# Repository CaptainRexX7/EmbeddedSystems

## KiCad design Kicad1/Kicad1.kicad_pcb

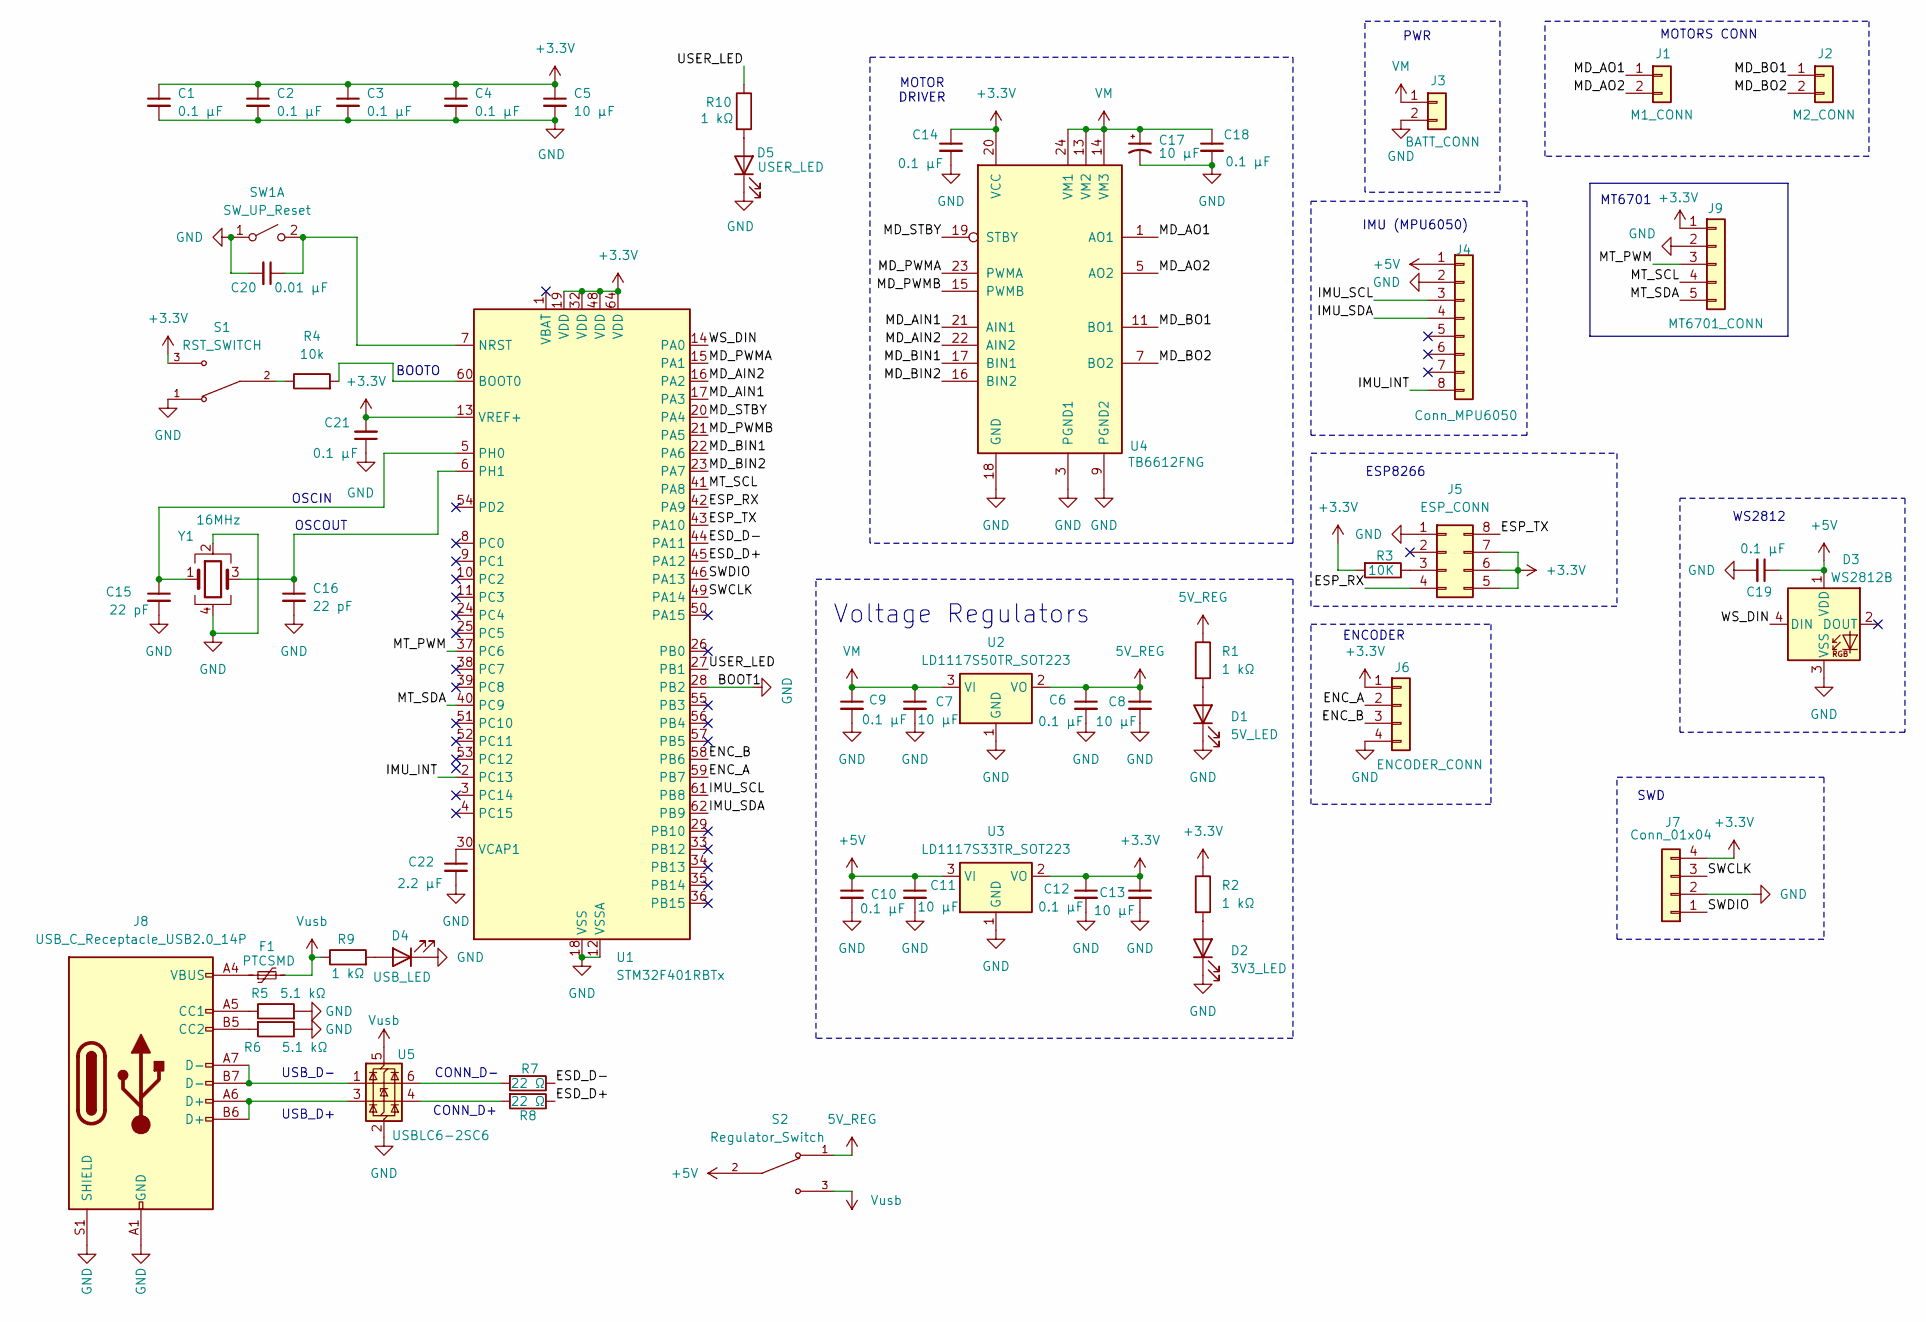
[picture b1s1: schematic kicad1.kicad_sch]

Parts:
C1, C2, C3, C4, C6, C9, C10, C12, C14, C18, C19, C21: 0.1 µF; C_0805_2012Metric_Pad1.18x1.45mm_HandSolder; Mfr#: KYOCERAAVX
C5: 10 µF; C_0805_2012Metric_Pad1.18x1.45mm_HandSolder
C7, C8, C11, C13: 10 µF; C_0805_2012Metric_Pad1.18x1.45mm_HandSolder; Mfr#: KYOCERAAVX
C15, C16: 22 pF; C_0805_2012Metric_Pad1.18x1.45mm_HandSolder
C17: 10 µF; CP_EIA-6032-28_Kemet-C_HandSolder
C20: 0.01 µF; C_0805_2012Metric_Pad1.18x1.45mm_HandSolder; Mfr#: KYOCERAAVX
C22: 2.2 µF; C_0805_2012Metric_Pad1.18x1.45mm_HandSolder
D1: 5V_LED; LED_0805_2012Metric_Pad1.15x1.40mm_HandSolder
D2: 3V3_LED; LED_0805_2012Metric_Pad1.15x1.40mm_HandSolder
D3: WS2812B; LED_WS2812B_PLCC4_5.0x5.0mm_P3.2mm
D4: USB_LED; LED_0805_2012Metric_Pad1.15x1.40mm_HandSolder
D5: USER_LED; LED_0805_2012Metric_Pad1.15x1.40mm_HandSolder
F1: PTCSMD; Fuse_1812_4532Metric
J1: M1_CONN; JST_XH_B2B-XH-A_1x02_P2.50mm_Vertical
J2: M2_CONN; JST_XH_B2B-XH-A_1x02_P2.50mm_Vertical
J3: BATT_CONN; JST_XH_B2B-XH-A_1x02_P2.50mm_Vertical
J4: Conn_MPU6050; PinSocket_1x08_P2.54mm_Vertical
J5: ESP_CONN; PinSocket_2x04_P2.54mm_Vertical
J6: ENCODER_CONN; JST_XH_B4B-XH-A_1x04_P2.50mm_Vertical
J7: Conn_01x04; PinHeader_1x04_P2.54mm_Vertical
J8: USB_C_Receptacle_USB2.0_14P; USB_C_Receptacle_HCTL_HC-TYPE-C-16P-01A
J9: MT6701_CONN; JST_XH_B5B-XH-A_1x05_P2.50mm_Vertical
R1, R2, R9, R10: 1 kΩ; R_0805_2012Metric_Pad1.20x1.40mm_HandSolder
R3: 10K; R_0805_2012Metric_Pad1.20x1.40mm_HandSolder
R4: 10k; R_0805_2012Metric_Pad1.20x1.40mm_HandSolder
R5, R6: 5.1 kΩ; R_0603_1608Metric_Pad0.98x0.95mm_HandSolder
R7, R8: 22 Ω; R_0805_2012Metric_Pad1.20x1.40mm_HandSolder
S1: RST_SWITCH; SW_SLW-66527511-SMT-TR; PARTREV 1.01
S2: Regulator_Switch; SW_SLW-66527511-SMT-TR; PARTREV 1.01
SW1: SW_UP_Reset; SW_uP_Reset
U1: STM32F401RBTx; LQFP-64_10x10mm_P0.5mm; mfr# STM32F401RET6
U2: LD1117S50TR_SOT223; SOT-223-3_TabPin2
U3: LD1117S33TR_SOT223; SOT-223-3_TabPin2
U4: TB6612FNG; SSOP-24_5.3x8.2mm_P0.65mm
U5: USBLC6-2SC6; SOT-23-6
Y1: 16MHz; Crystal_SMD_Abracon_ABM8G-4Pin_3.2x2.5mm

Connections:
5V_REG: C6.1, C8.1, R1.1, S2.1, U2.2 (VO)
+3.3V: C1.1, C2.1, C3.1, C4.1, C5.1, C12.1, C13.1, C14.1, C21.2, J5.5, J5.6, J5.7, J6.1, J7.4, J9.1, R2.1, R3.2, S1.3, U1.13 (VREF+), U1.19 (VDD), U1.32 (VDD), U1.48 (VDD), U1.64 (VDD), U3.2 (VO), U4.20 (VCC)
+5V: C10.1, C11.1, C19.1, D3.1 (VDD), J4.1, S2.2, U3.3 (VI)
/ENC_A: J6.2, U1.59 (PB7)
/ENC_B: J6.3, U1.58 (PB6)
/ESD_D+: R8.1, U1.45 (PA12)
/ESD_D-: R7.1, U1.44 (PA11)
/ESP_RX: J5.4, U1.42 (PA9)
/ESP_TX: J5.8, U1.43 (PA10)
/IMU_INT: J4.8, U1.2 (PC13)
/IMU_SCL: J4.3, U1.61 (PB8)
/IMU_SDA: J4.4, U1.62 (PB9)
/MD_AIN1: U1.17 (PA3), U4.21 (AIN1)
/MD_AIN2: U1.16 (PA2), U4.22 (AIN2)
/MD_AO1: J1.1, U4.1 (AO1), U4.2 (AO1)
/MD_AO2: J1.2, U4.5 (AO2), U4.6 (AO2)
/MD_BIN1: U1.22 (PA6), U4.17 (BIN1)
/MD_BIN2: U1.23 (PA7), U4.16 (BIN2)
/MD_BO1: J2.1, U4.11 (BO1), U4.12 (BO1)
/MD_BO2: J2.2, U4.7 (BO2), U4.8 (BO2)
/MD_PWMA: U1.15 (PA1), U4.23 (PWMA)
/MD_PWMB: U1.21 (PA5), U4.15 (PWMB)
/MD_STBY: U1.20 (PA4), U4.19 (STBY)
/MT_PWM: J9.3, U1.37 (PC6)
/MT_SCL: J9.4, U1.41 (PA8)
/MT_SDA: J9.5, U1.40 (PC9)
/SWCLK: J7.3, U1.49 (PA14)
/SWDIO: J7.1, U1.46 (PA13)
/USER_LED: R10.1, U1.27 (PB1)
/WS_DIN: D3.4 (DIN), U1.14 (PA0)
GND: C1.2, C2.2, C3.2, C4.2, C5.2, C6.2, C7.2, C8.2, C9.2, C10.2, C11.2, C12.2, C13.2, C14.2, C15.2, C16.2, C17.2, C18.2, C19.2, C20.2, C21.1, C22.2, D1.1 (K), D2.1 (K), D3.3 (VSS), D4.1 (K), D5.1 (K), J3.2, J4.2, J5.1, J6.4, J7.2, J8.A1 (GND), J8.A12 (GND), J8.B1 (GND), J8.B12 (GND), J8.S1 (SHIELD), J9.2, R5.2, R6.1, S1.1, SW1.1 (A), U1.12 (VSSA), U1.18 (VSS), U1.28 (PB2), U1.31 (VSS), U1.47 (VSS), U1.63 (VSS), U2.1 (GND), U3.1 (GND), U4.3 (PGND1), U4.4 (PGND1), U4.9 (PGND2), U4.10 (PGND2), U4.18 (GND), U5.2 (GND), Y1.2, Y1.4
unnamed: D1.2 (A), R1.2
unnamed: D2.2 (A), R2.2
unnamed: D4.2 (A), R9.2
unnamed: D5.2 (A), R10.2
unnamed: F1.1, J8.A4 (VBUS), J8.A9 (VBUS), J8.B4 (VBUS), J8.B9 (VBUS)
unnamed: J5.3, R3.1
unnamed: J8.A5 (CC1), R5.1
unnamed: J8.B5 (CC2), R6.2
unnamed: J8.A6 (D+), J8.B6 (D+), U5.3 (I/O2)
unnamed: J8.A7 (D-), J8.B7 (D-), U5.1 (I/O1)
unnamed: R4.1, S1.2
unnamed: R7.2, U5.6 (I/O1)
unnamed: R8.2, U5.4 (I/O2)
unnamed: C20.1, SW1.2 (B), U1.7 (NRST)
unnamed: R4.2, U1.60 (BOOT0)
unnamed: C15.1, U1.5 (PH0), Y1.1
unnamed: C16.1, U1.6 (PH1), Y1.3
unnamed: C22.1, U1.30 (VCAP1)
VM: C7.1, C9.1, C17.1, C18.1, J3.1, U2.3 (VI), U4.13 (VM2), U4.14 (VM3), U4.24 (VM1)
Vusb: F1.2, R9.1, S2.3, U5.5 (VBUS)

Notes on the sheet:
OSCIN
Voltage Regulators
PWR
MT6701
SWD
CONN_D+
ENCODER
ESP8266
CONN_D-
MOTOR DRIVER
OSCOUT
IMU (MPU6050)
WS2812
BOOTO
MOTORS CONN
USB_D+
USB_D-

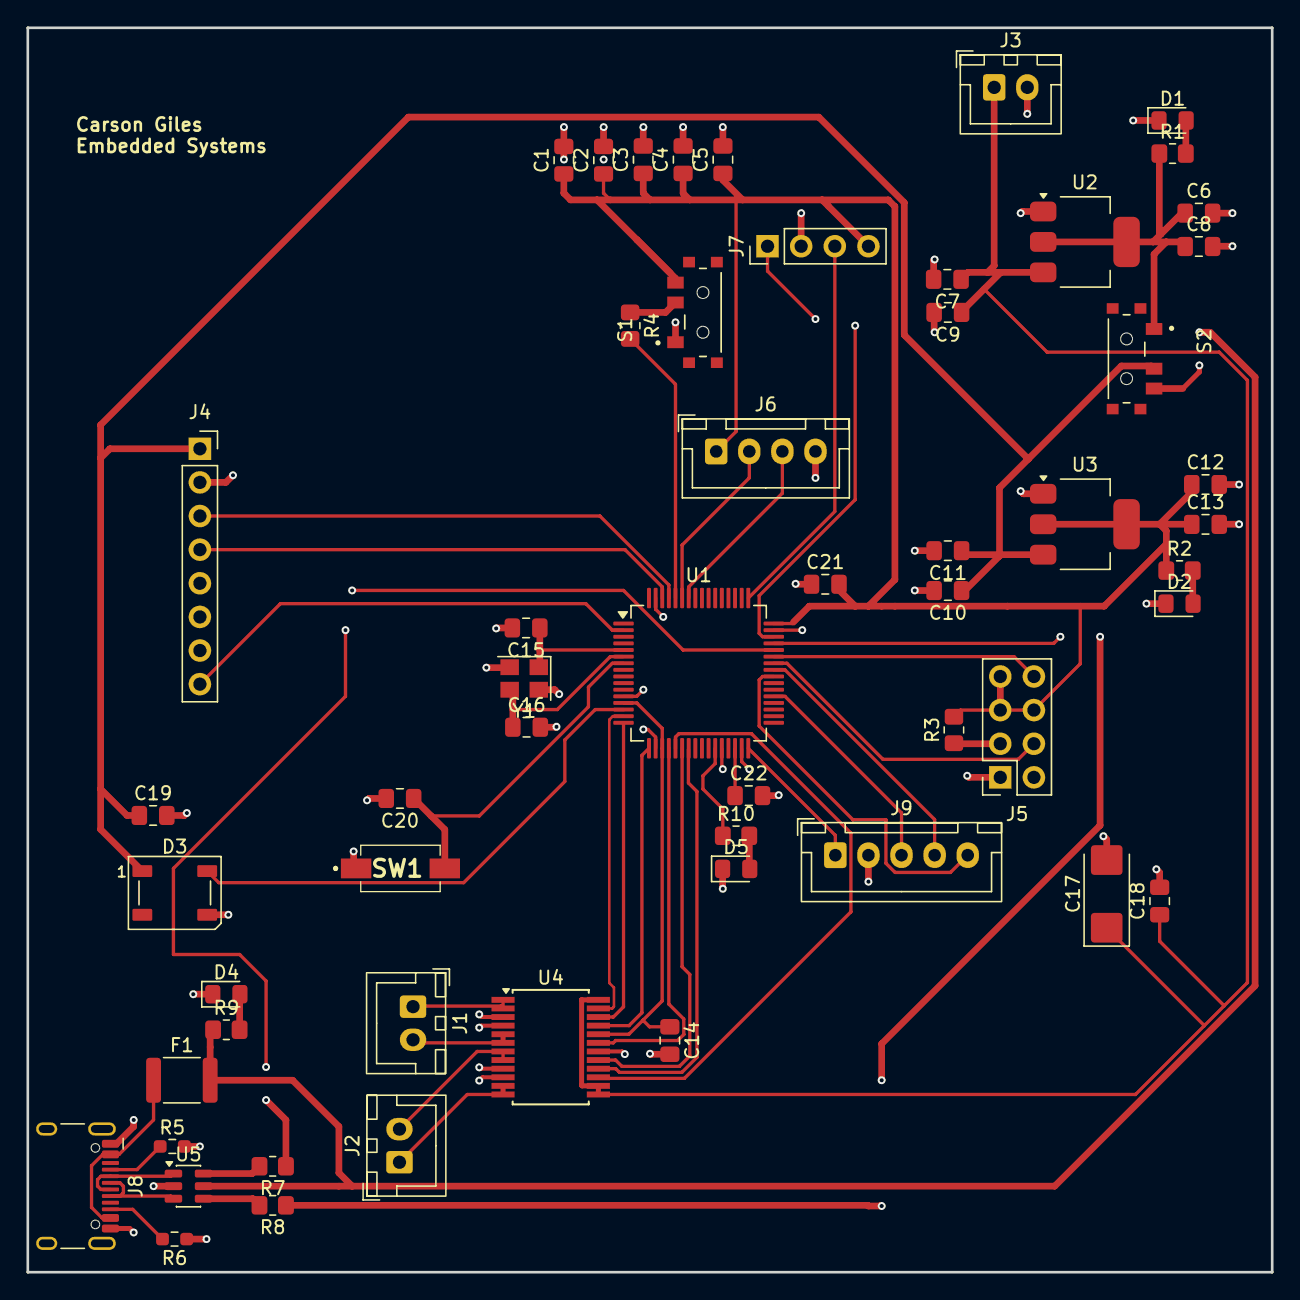
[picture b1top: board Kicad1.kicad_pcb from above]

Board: 2 copper layers, 94.0 x 94.0 mm, 56 parts (0 on the bottom side), 51 nets.

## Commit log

2026-04-23 Add files via upload
    I messed up the name and haven't fixed it yet so its called untiled.
2026-04-30 Create Docs
